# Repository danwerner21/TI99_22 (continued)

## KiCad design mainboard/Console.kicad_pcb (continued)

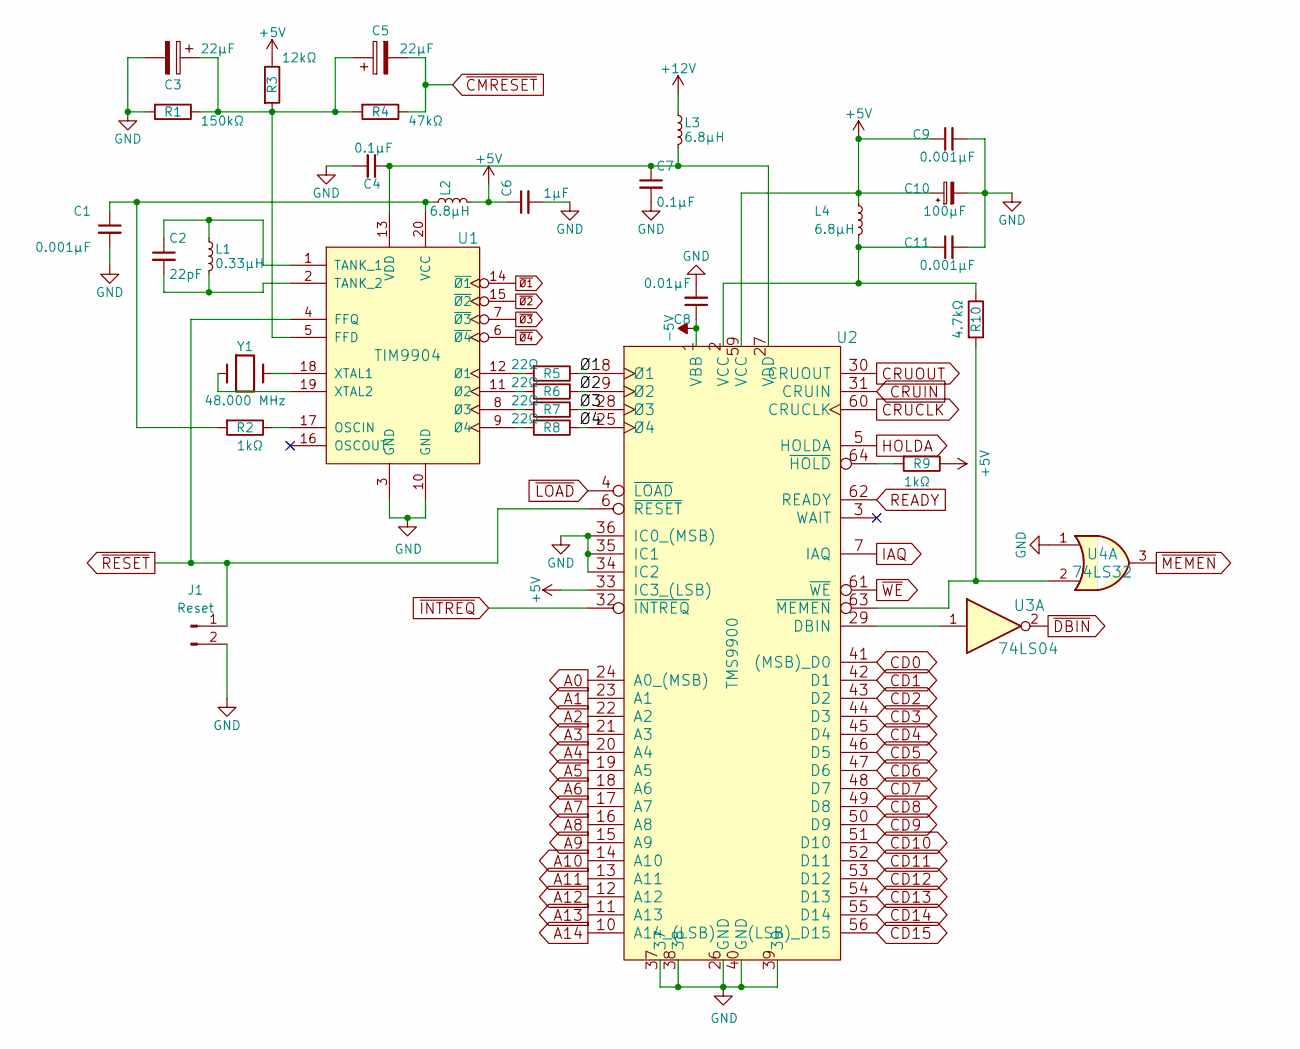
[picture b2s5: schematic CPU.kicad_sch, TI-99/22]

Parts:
C1, C9, C11: 0.001µF; C_Rect_L7.0mm_W2.0mm_P5.00mm
C2: 22pF; C_Rect_L7.0mm_W2.0mm_P5.00mm
C3, C5: 22µF; CP_Radial_D7.5mm_P2.50mm
C4, C7: 0.1µF; C_Rect_L7.0mm_W2.0mm_P5.00mm
C6: 1µF; C_Rect_L7.0mm_W2.0mm_P5.00mm
C8: 0.01µF; C_Rect_L7.0mm_W2.0mm_P5.00mm
C10: 100µF; CP_Radial_D7.5mm_P2.50mm
J1: Reset; PinHeader_1x02_P2.54mm_Vertical
L1: 0.33µH; R_Axial_DIN0207_L6.3mm_D2.5mm_P7.62mm_Horizontal
L2, L3, L4: 6.8µH; R_Axial_DIN0207_L6.3mm_D2.5mm_P7.62mm_Horizontal
R1: 150kΩ; R_Axial_DIN0207_L6.3mm_D2.5mm_P7.62mm_Horizontal
R2, R9: 1kΩ; R_Axial_DIN0207_L6.3mm_D2.5mm_P7.62mm_Horizontal
R3: 12kΩ; R_Axial_DIN0207_L6.3mm_D2.5mm_P7.62mm_Horizontal
R4: 47kΩ; R_Axial_DIN0207_L6.3mm_D2.5mm_P7.62mm_Horizontal
R5, R6, R7, R8: 22Ω; R_Axial_DIN0207_L6.3mm_D2.5mm_P7.62mm_Horizontal
R10: 4.7kΩ; R_Axial_DIN0207_L6.3mm_D2.5mm_P7.62mm_Horizontal
U1: TIM9904; DIP-20_W7.62mm_Socket_LongPads
U2: TMS9900; DIP-64_W22.86mm_Socket_LongPads
U3: 74LS04; DIP-14_W7.62mm_Socket_LongPads
U4: 74LS32; DIP-14_W7.62mm_Socket_LongPads
Y1: 48.000 MHz; Crystal_HC49-U_Vertical

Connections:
+5V: C6.1, C9.1, C10.1, L2.2, L4.1, R3.1, R9.1, U2.33 (IC3_(LSB)), U2.59 (VCC); also elsewhere on the board
+12V: L3.1; also elsewhere on the board
-5V: C8.1, U2.1 (VBB); also elsewhere on the board
/CPU/Ø1: R5.1, U2.8 (Ø1)
/CPU/Ø2: R6.1, U2.9 (Ø2)
/CPU/Ø3: R7.1, U2.28 (Ø3)
/CPU/Ø4: R8.1, U2.25 (Ø4)
A0: U2.24 (A0_(MSB)); also elsewhere on the board
A1: U2.23 (A1); also elsewhere on the board
A2: U2.22 (A2); also elsewhere on the board
A3: U2.21 (A3); also elsewhere on the board
A4: U2.20 (A4); also elsewhere on the board
A5: U2.19 (A5); also elsewhere on the board
A6: U2.18 (A6); also elsewhere on the board
A7: U2.17 (A7); also elsewhere on the board
A8: U2.16 (A8); also elsewhere on the board
A9: U2.15 (A9); also elsewhere on the board
A10: U2.14 (A10); also elsewhere on the board
A11: U2.13 (A11); also elsewhere on the board
A12: U2.12 (A12); also elsewhere on the board
A13: U2.11 (A13); also elsewhere on the board
A14: U2.10 (A14_(LSB)); also elsewhere on the board
CD0: U2.41 ((MSB)_D0); also elsewhere on the board
CD1: U2.42 (D1); also elsewhere on the board
CD2: U2.43 (D2); also elsewhere on the board
CD3: U2.44 (D3); also elsewhere on the board
CD4: U2.45 (D4); also elsewhere on the board
CD5: U2.46 (D5); also elsewhere on the board
CD6: U2.47 (D6); also elsewhere on the board
CD7: U2.48 (D7); also elsewhere on the board
CD8: U2.49 (D8); also elsewhere on the board
CD9: U2.50 (D9); also elsewhere on the board
CD10: U2.51 (D10); also elsewhere on the board
CD11: U2.52 (D11); also elsewhere on the board
CD12: U2.53 (D12); also elsewhere on the board
CD13: U2.54 (D13); also elsewhere on the board
CD14: U2.55 (D14); also elsewhere on the board
CD15: U2.56 ((LSB)_D15); also elsewhere on the board
CRUCLK: U2.60 (CRUCLK); also elsewhere on the board
CRUIN: U2.31 (CRUIN); also elsewhere on the board
CRUOUT: U2.30 (CRUOUT); also elsewhere on the board
HOLDA: U2.5 (HOLDA); also elsewhere on the board
IAQ: U2.7 (IAQ); also elsewhere on the board
unnamed: C1.1, L2.1, R2.2, U1.20 (VCC)
unnamed: C2.1, L1.1, U1.1 (TANK_1)
unnamed: C2.2, L1.2, U1.2 (TANK_2)
unnamed: C3.1, C5.1, R1.1, R3.2, R4.2, U1.5 (FFD)
unnamed: C4.1, C7.1, L3.2, U1.13 (VDD), U2.27 (VDD)
unnamed: C11.1, L4.2, R10.1, U2.2 (VCC)
unnamed: R2.1, U1.17 (OSCIN)
unnamed: R5.2, U1.12 (Ø1)
unnamed: R6.2, U1.11 (Ø2)
unnamed: R7.2, U1.8 (Ø3)
unnamed: R8.2, U1.9 (Ø4)
unnamed: R9.2, U2.64 (~HOLD)
unnamed: R10.2, U2.63 (~MEMEN), U4.2
unnamed: U1.18 (XTAL1), Y1.2
unnamed: U1.19 (XTAL2), Y1.1
unnamed: U2.29 (DBIN), U3.1
READY: U2.62 (READY); also elsewhere on the board
VRAM_BANK: C1.2, C3.2, C4.2, C6.2, C7.2, C8.2, C9.2, C10.2, C11.2, J1.2, R1.2, U1.3 (GND), U1.10 (GND), U2.26 (GND), U2.34 (IC2), U2.35 (IC1), U2.36 (IC0_(MSB)), U2.37, U2.38, U2.39, U2.40 (GND), U4.1; also elsewhere on the board
~CMRESET: C5.2, R4.1; also elsewhere on the board
~DBIN: U3.2; also elsewhere on the board
~INTREQ: U2.32 (~INTREQ); also elsewhere on the board
~LOAD: U2.4 (~LOAD); also elsewhere on the board
~MEMEN: U4.3; also elsewhere on the board
~RESET: J1.1, U1.4 (FFQ), U2.6 (~RESET); also elsewhere on the board
~WE: U2.61 (~WE); also elsewhere on the board
~Ø1: U1.14 (~Ø1); also elsewhere on the board
~Ø2: U1.15 (~Ø2); also elsewhere on the board
~Ø3: U1.7 (~Ø3); also elsewhere on the board
~Ø4: U1.6 (~Ø4); also elsewhere on the board

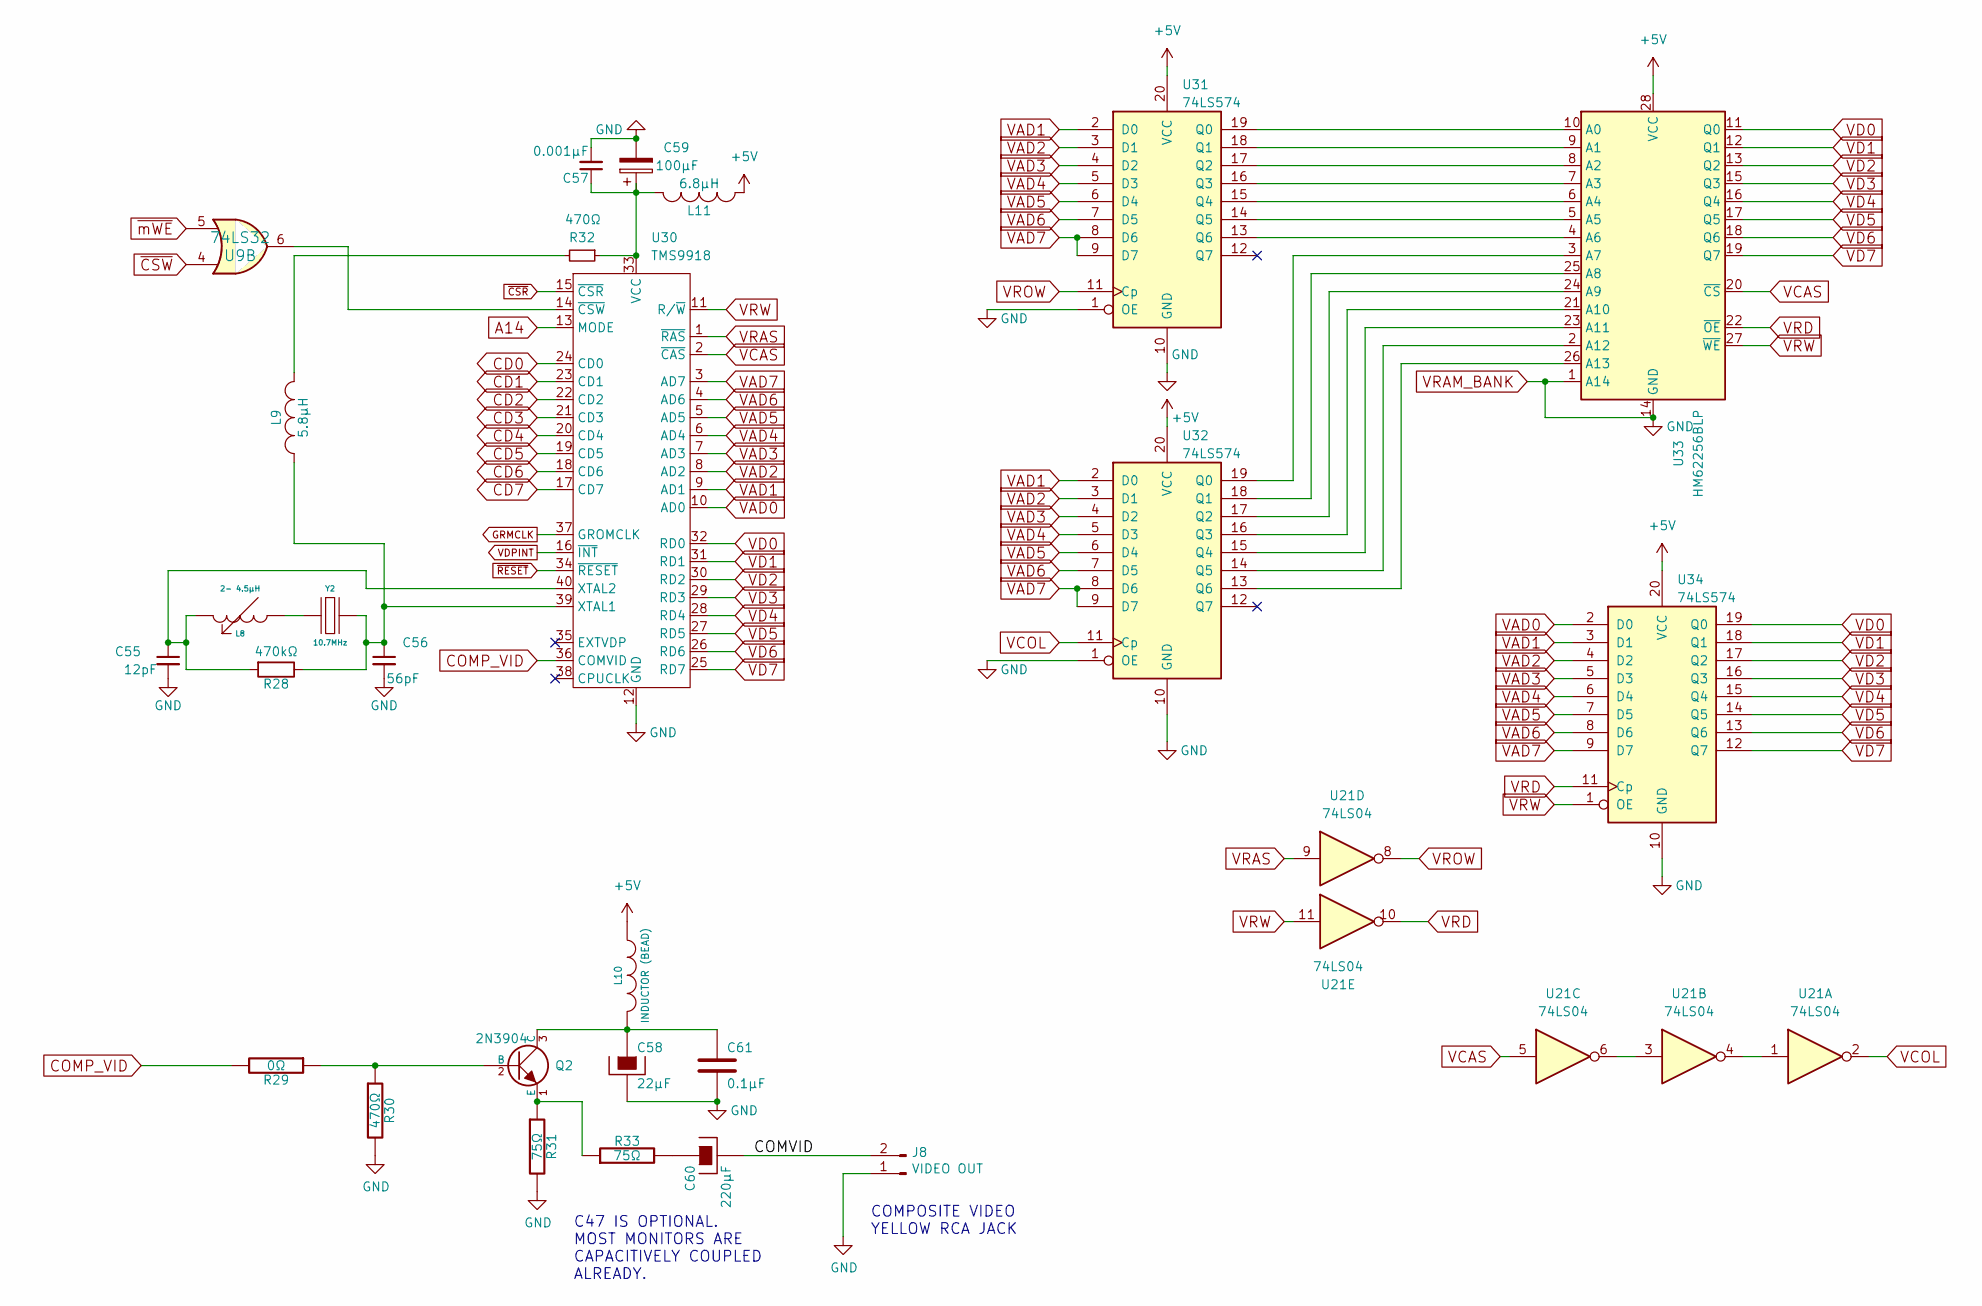
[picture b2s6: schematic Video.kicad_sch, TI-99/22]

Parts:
C55: 12pF; C_Rect_L7.0mm_W2.0mm_P5.00mm
C56: 56pF; C_Rect_L7.0mm_W2.0mm_P5.00mm
C57: 0.001µF; C_Rect_L7.0mm_W2.0mm_P5.00mm
C58: 22µF; CP_Radial_D7.5mm_P2.50mm
C59: 100µF; CP_Radial_D7.5mm_P2.50mm
C60: 220µF; CP_Radial_D7.5mm_P2.50mm
C61: 0.1µF; C_Rect_L7.0mm_W2.0mm_P5.00mm
J8: VIDEO OUT; PinHeader_1x02_P2.54mm_Vertical
L8: 2- 4.5µH; R_Axial_DIN0207_L6.3mm_D2.5mm_P7.62mm_Horizontal
L9: 5.8µH; R_Axial_DIN0207_L6.3mm_D2.5mm_P7.62mm_Horizontal
L10: INDUCTOR (BEAD); R_Axial_DIN0207_L6.3mm_D2.5mm_P10.16mm_Horizontal
L11: 6.8µH; R_Axial_DIN0207_L6.3mm_D2.5mm_P7.62mm_Horizontal
Q2: 2N3904; TO-92L_HandSolder
R28: 470kΩ; R_Axial_DIN0207_L6.3mm_D2.5mm_P7.62mm_Horizontal
R29: 0Ω; R_Axial_DIN0207_L6.3mm_D2.5mm_P7.62mm_Horizontal
R30, R32: 470Ω; R_Axial_DIN0207_L6.3mm_D2.5mm_P7.62mm_Horizontal
R31, R33: 75Ω; R_Axial_DIN0207_L6.3mm_D2.5mm_P7.62mm_Horizontal
U9: 74LS32; DIP-14_W7.62mm_Socket_LongPads
U21: 74LS04; DIP-14_W7.62mm_Socket_LongPads
U30: TMS9918; DIP-40_W15.24mm_Socket_LongPads
U31, U32, U34: 74LS574; DIP-20_W7.62mm_Socket_LongPads
U33: HM62256BLP; DIP-28_W15.24mm_Socket_LongPads
Y2: 10.7MHz; Crystal_HC49-U_Vertical

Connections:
+5V: L10.1, L11.2, U31.20 (VCC), U32.20 (VCC), U33.28 (VCC), U34.20 (VCC); also elsewhere on the board
/Video/COMVID: C60.2, J8.2
A14: U30.13 (MODE); also elsewhere on the board
CD0: U30.24 (CD0); also elsewhere on the board
CD1: U30.23 (CD1); also elsewhere on the board
CD2: U30.22 (CD2); also elsewhere on the board
CD3: U30.21 (CD3); also elsewhere on the board
CD4: U30.20 (CD4); also elsewhere on the board
CD5: U30.19 (CD5); also elsewhere on the board
CD6: U30.18 (CD6); also elsewhere on the board
CD7: U30.17 (CD7); also elsewhere on the board
COMP_VID: R29.2, U30.36 (COMVID)
GRMCLK: U30.37 (GROMCLK); also elsewhere on the board
unnamed: C55.1, L8.2, R28.2, U30.40 (XTAL2)
unnamed: C56.1, L9.1, R28.1, U30.39 (XTAL1), Y2.2
unnamed: C57.1, C59.1, L11.1, R32.1, U30.33 (VCC)
unnamed: C58.1, C61.1, L10.2, Q2.3 (C)
unnamed: C60.1, R33.2
unnamed: L8.1, Y2.1
unnamed: L9.2, R32.2
unnamed: Q2.1 (E), R31.1, R33.1
unnamed: Q2.2 (B), R29.1, R30.1
unnamed: U21.1, U21.4
unnamed: U21.3, U21.6
unnamed: U9.6, U30.14 (~CSW)
unnamed: U31.13 (Q6), U33.4 (A6)
unnamed: U31.14 (Q5), U33.5 (A5)
unnamed: U31.15 (Q4), U33.6 (A4)
unnamed: U31.16 (Q3), U33.7 (A3)
unnamed: U31.17 (Q2), U33.8 (A2)
unnamed: U31.18 (Q1), U33.9 (A1)
unnamed: U31.19 (Q0), U33.10 (A0)
unnamed: U32.13 (Q6), U33.26 (A13)
unnamed: U32.14 (Q5), U33.2 (A12)
unnamed: U32.15 (Q4), U33.23 (A11)
unnamed: U32.16 (Q3), U33.21 (A10)
unnamed: U32.17 (Q2), U33.24 (A9)
unnamed: U32.18 (Q1), U33.25 (A8)
unnamed: U32.19 (Q0), U33.3 (A7)
VAD0: U30.10 (AD0), U34.2 (D0)
VAD1: U30.9 (AD1), U31.2 (D0), U32.2 (D0), U34.3 (D1)
VAD2: U30.8 (AD2), U31.3 (D1), U32.3 (D1), U34.4 (D2)
VAD3: U30.7 (AD3), U31.4 (D2), U32.4 (D2), U34.5 (D3)
VAD4: U30.6 (AD4), U31.5 (D3), U32.5 (D3), U34.6 (D4)
VAD5: U30.5 (AD5), U31.6 (D4), U32.6 (D4), U34.7 (D5)
VAD6: U30.4 (AD6), U31.7 (D5), U32.7 (D5), U34.8 (D6)
VAD7: U30.3 (AD7), U31.8 (D6), U31.9 (D7), U32.8 (D6), U32.9 (D7), U34.9 (D7)
VCAS: U21.5, U30.2 (~CAS), U33.20 (~CS)
VCOL: U21.2, U32.11 (Cp)
VD0: U30.32 (RD0), U33.11 (Q0), U34.19 (Q0)
VD1: U30.31 (RD1), U33.12 (Q1), U34.18 (Q1)
VD2: U30.30 (RD2), U33.13 (Q2), U34.17 (Q2)
VD3: U30.29 (RD3), U33.15 (Q3), U34.16 (Q3)
VD4: U30.28 (RD4), U33.16 (Q4), U34.15 (Q4)
VD5: U30.27 (RD5), U33.17 (Q5), U34.14 (Q5)
VD6: U30.26 (RD6), U33.18 (Q6), U34.13 (Q6)
VD7: U30.25 (RD7), U33.19 (Q7), U34.12 (Q7)
VDPINT: U30.16 (~INT); also elsewhere on the board
VRAM_BANK: C55.2, C56.2, C57.2, C58.2, C59.2, C61.2, J8.1, R30.2, R31.2, U30.12 (GND), U31.1 (OE), U31.10 (GND), U32.1 (OE), U32.10 (GND), U33.1 (A14), U33.14 (GND), U34.10 (GND); also elsewhere on the board
VRAS: U21.9, U30.1 (~RAS)
VRD: U21.10, U33.22 (~OE), U34.11 (Cp)
VROW: U21.8, U31.11 (Cp)
VRW: U21.11, U30.11 (R/~W), U33.27 (~WE), U34.1 (OE)
~CSR: U30.15 (~CSR); also elsewhere on the board
~CSW: U9.4; also elsewhere on the board
~RESET: U30.34 (~RESET); also elsewhere on the board
~mWE: U9.5; also elsewhere on the board

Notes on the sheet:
COMPOSITE VIDEO YELLOW RCA JACK
C47 IS OPTIONAL. MOST MONITORS ARE CAPACITIVELY COUPLED ALREADY.

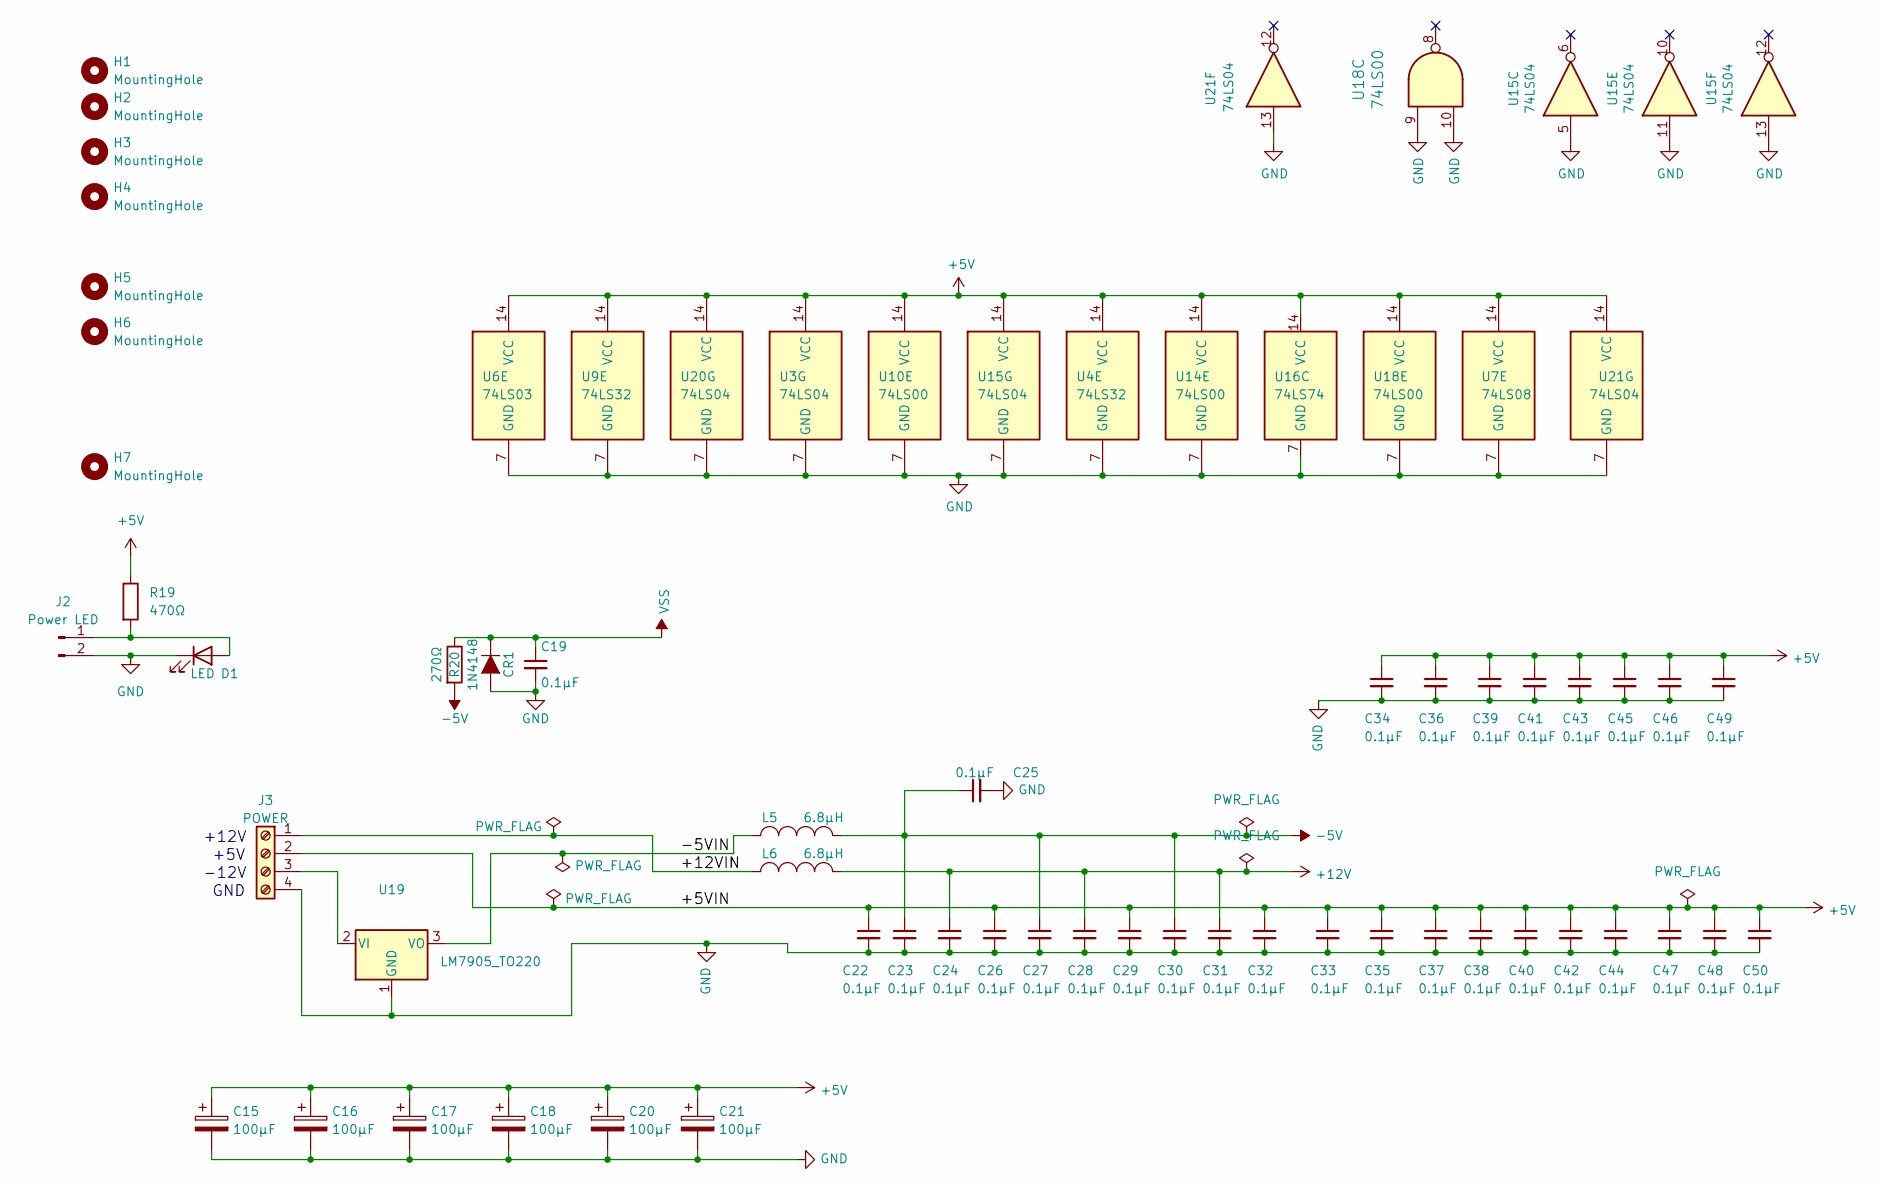
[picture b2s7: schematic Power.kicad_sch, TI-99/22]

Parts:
C15, C16, C17, C18, C20, C21: 100µF; CP_Radial_D7.5mm_P2.50mm
C19, C22, C23, C24, C25, C26, C27, C28, C29, C30, C31, C32, C33, C34, C35, C36, C37, C38, C39, C40, C41, C42, C43, C44, C45, C46, C47, C48, C49, C50: 0.1µF; C_Rect_L7.0mm_W2.0mm_P5.00mm
CR1: 1N4148; D_A-405_P7.62mm_Horizontal
D1: LED; LED_D5.0mm
H1, H2, H3, H4, H5, H6, H7: MountingHole; MountingHole_3.2mm_M3
J2: Power LED; PinHeader_1x02_P2.54mm_Vertical
J3: POWER; TerminalBlock_RND_205-00278_1x04_P5.00mm_Vertical
L5, L6: 6.8µH; R_Axial_DIN0207_L6.3mm_D2.5mm_P7.62mm_Horizontal
R19: 470Ω; R_Axial_DIN0207_L6.3mm_D2.5mm_P7.62mm_Horizontal
R20: 270Ω; R_Axial_DIN0207_L6.3mm_D2.5mm_P7.62mm_Horizontal
U3, U15, U20, U21: 74LS04; DIP-14_W7.62mm_Socket_LongPads
U4, U9: 74LS32; DIP-14_W7.62mm_Socket_LongPads
U6: 74LS03; DIP-14_W7.62mm_Socket_LongPads
U7: 74LS08; DIP-14_W7.62mm_Socket_LongPads
U10, U14, U18: 74LS00; DIP-14_W7.62mm_Socket_LongPads
U16: 74LS74; DIP-14_W7.62mm_Socket_LongPads
U19: LM7905_TO220; TO-220-3_Vertical

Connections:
+5V: C15.1, C16.1, C17.1, C18.1, C20.1, C21.1, C22.1, C26.1, C29.1, C32.1, C33.1, C34.1, C35.1, C36.1, C37.1, C38.1, C39.1, C40.1, C41.1, C42.1, C43.1, C44.1, C45.1, C46.1, C47.1, C48.1, C49.1, C50.1, J3.2, R19.1, U3.14 (VCC), U4.14 (VCC), U6.14 (VCC), U7.14 (VCC), U9.14 (VCC), U10.14 (VCC), U14.14 (VCC), U15.14 (VCC), U16.14 (VCC), U18.14 (VCC), U20.14 (VCC), U21.14 (VCC); also elsewhere on the board
+12V: C24.1, C28.1, C31.1, L6.1; also elsewhere on the board
-5V: C23.1, C25.1, C27.1, C30.1, L5.1, R20.2; also elsewhere on the board
/Power/+12VIN: J3.1, L6.2
/Power/-5VIN: L5.2, U19.3 (VO)
unnamed: D1.2 (A), J2.1, R19.2
unnamed: J3.3, U19.2 (VI)
VRAM_BANK: C15.2, C16.2, C17.2, C18.2, C19.2, C20.2, C21.2, C22.2, C23.2, C24.2, C25.2, C26.2, C27.2, C28.2, C29.2, C30.2, C31.2, C32.2, C33.2, C34.2, C35.2, C36.2, C37.2, C38.2, C39.2, C40.2, C41.2, C42.2, C43.2, C44.2, C45.2, C46.2, C47.2, C48.2, C49.2, C50.2, CR1.2 (A), D1.1 (K), J2.2, J3.4, U3.7 (GND), U4.7 (GND), U6.7 (GND), U7.7 (GND), U9.7 (GND), U10.7 (GND), U14.7 (GND), U15.5, U15.7 (GND), U15.11, U15.13, U16.7 (GND), U18.7 (GND), U18.9, U18.10, U19.1 (GND), U20.7 (GND), U21.7 (GND), U21.13; also elsewhere on the board
VSS: C19.1, CR1.1 (K), R20.1; also elsewhere on the board

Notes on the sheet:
-12V
+5V
GND
+12V

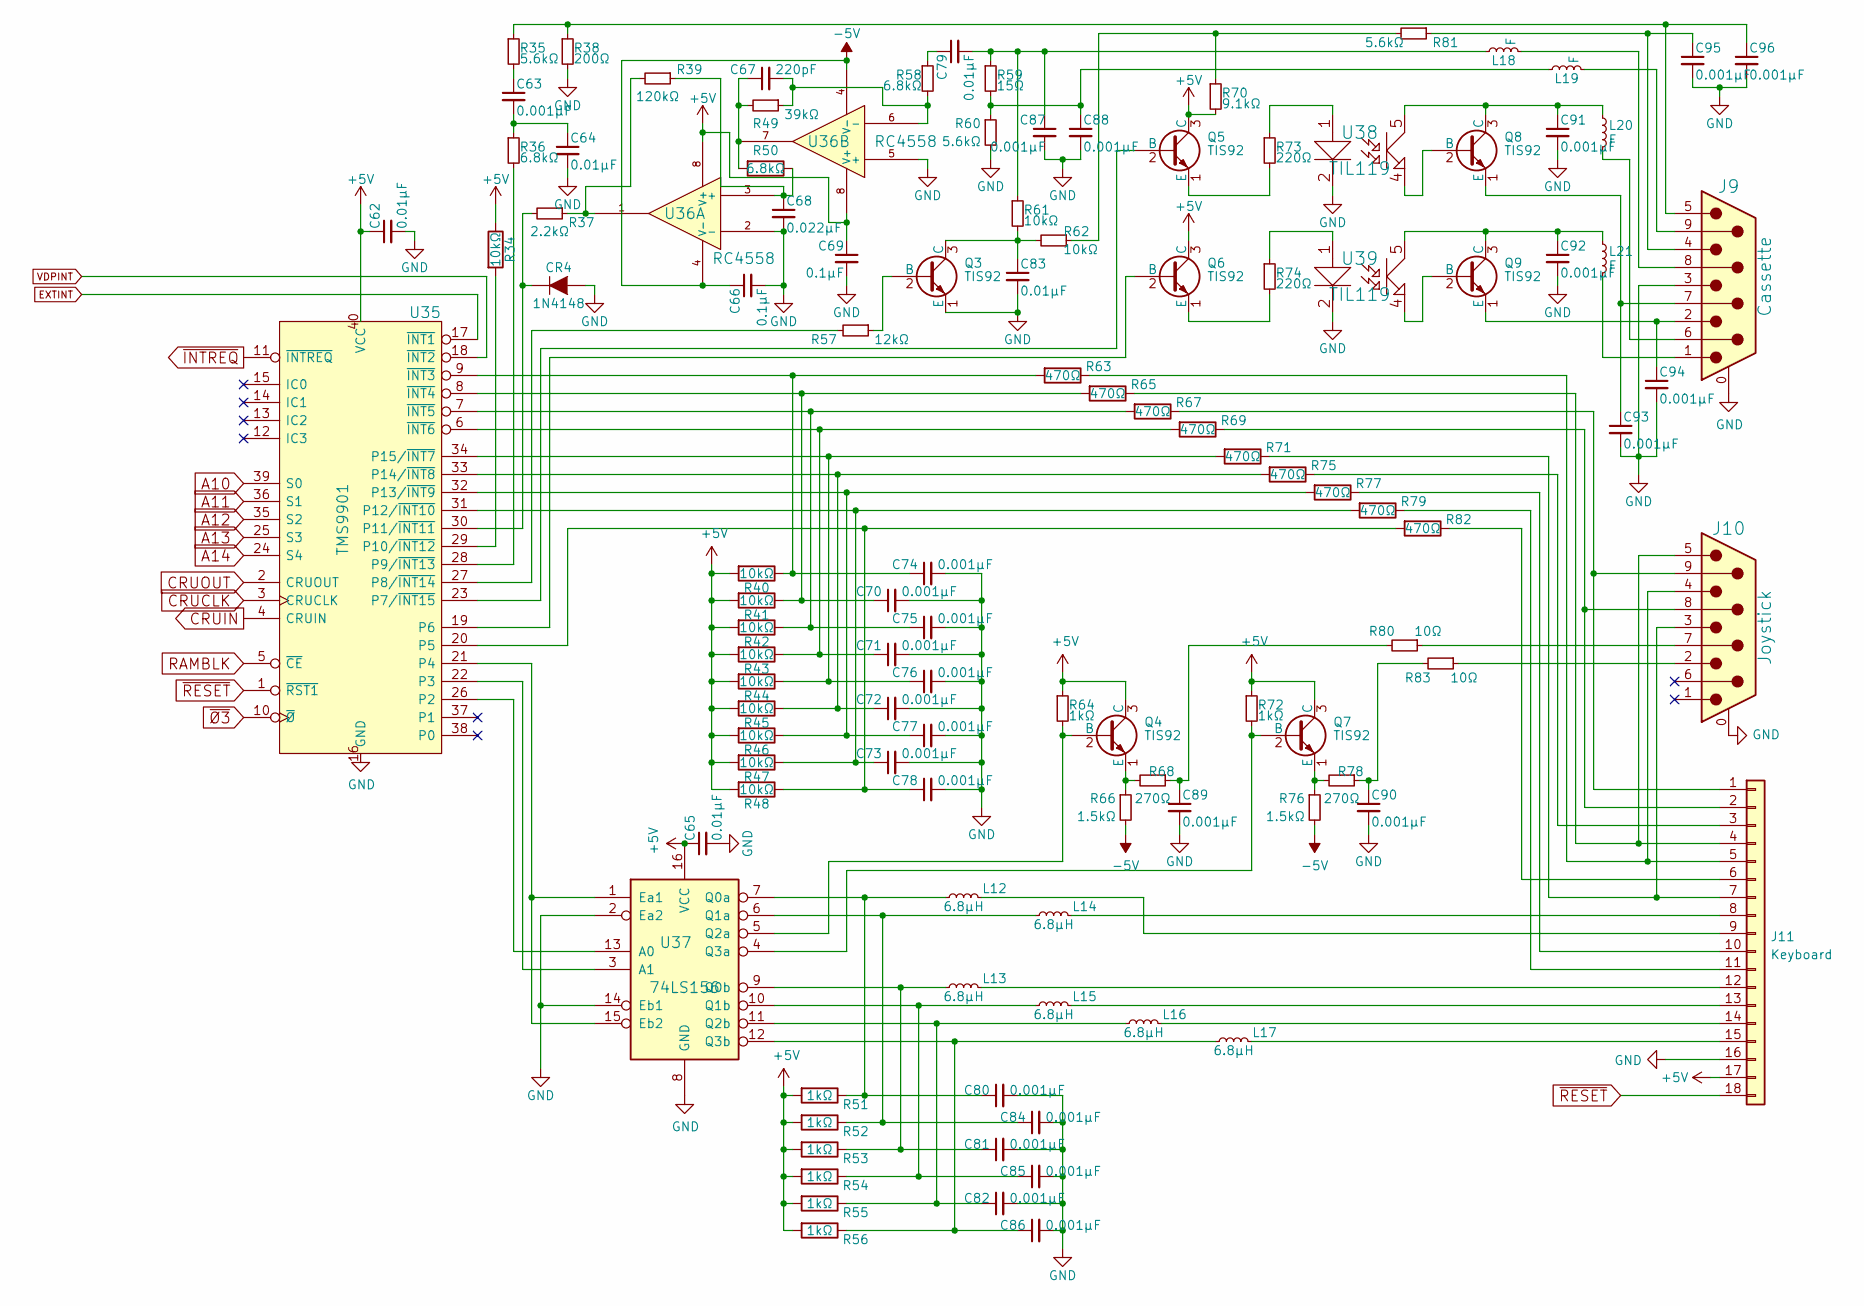
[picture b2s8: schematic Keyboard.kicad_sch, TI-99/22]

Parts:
C62, C64, C65, C79, C83: 0.01µF; C_Rect_L7.0mm_W2.0mm_P5.00mm
C63, C70, C71, C72, C73, C74, C75, C76, C77, C78, C80, C81, C82, C84, C85, C86, C87, C88, C89, C90, C91, C92, C93, C94, C95, C96: 0.001µF; C_Rect_L7.0mm_W2.0mm_P5.00mm
C66, C69: 0.1µF; C_Rect_L7.0mm_W2.0mm_P5.00mm
C67: 220pF; C_Rect_L7.0mm_W2.0mm_P5.00mm
C68: 0.022µF; C_Rect_L7.0mm_W2.0mm_P5.00mm
CR4: 1N4148; D_A-405_P7.62mm_Horizontal
J9: Cassette; DSUB-9_Female_Horizontal_P2.77x2.84mm_EdgePinOffset4.94mm_H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
J10: Joystick; DSUB-9_Female_Horizontal_P2.77x2.84mm_EdgePinOffset4.94mm_H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
J11: Keyboard; PinHeader_1x18_P2.54mm_Vertical
L12, L13, L14, L15, L16, L17: 6.8µH; R_Axial_DIN0207_L6.3mm_D2.5mm_P7.62mm_Horizontal
L18, L19, L20, L21: F; R_Axial_DIN0207_L6.3mm_D2.5mm_P7.62mm_Horizontal
Q3, Q4, Q5, Q6, Q7, Q8, Q9: TIS92; TO-92_HandSolder
R34, R40, R41, R42, R43, R44, R45, R46, R47, R48, R61, R62: 10kΩ; R_Axial_DIN0207_L6.3mm_D2.5mm_P7.62mm_Horizontal
R35, R60, R81: 5.6kΩ; R_Axial_DIN0207_L6.3mm_D2.5mm_P7.62mm_Horizontal
R36, R50, R58: 6.8kΩ; R_Axial_DIN0207_L6.3mm_D2.5mm_P7.62mm_Horizontal
R37: 2.2kΩ; R_Axial_DIN0207_L6.3mm_D2.5mm_P7.62mm_Horizontal
R38: 200Ω; R_Axial_DIN0207_L6.3mm_D2.5mm_P7.62mm_Horizontal
R39: 120kΩ; R_Axial_DIN0207_L6.3mm_D2.5mm_P7.62mm_Horizontal
R49: 39kΩ; R_Axial_DIN0207_L6.3mm_D2.5mm_P7.62mm_Horizontal
R51, R52, R53, R54, R55, R56, R64, R72: 1kΩ; R_Axial_DIN0207_L6.3mm_D2.5mm_P7.62mm_Horizontal
R57: 12kΩ; R_Axial_DIN0207_L6.3mm_D2.5mm_P7.62mm_Horizontal
R59: 15Ω; R_Axial_DIN0207_L6.3mm_D2.5mm_P7.62mm_Horizontal
R63, R65, R67, R69, R71, R75, R77, R79, R82: 470Ω; R_Axial_DIN0207_L6.3mm_D2.5mm_P7.62mm_Horizontal
R66, R76: 1.5kΩ; R_Axial_DIN0207_L6.3mm_D2.5mm_P7.62mm_Horizontal
R68, R78: 270Ω; R_Axial_DIN0207_L6.3mm_D2.5mm_P7.62mm_Horizontal
R70: 9.1kΩ; R_Axial_DIN0207_L6.3mm_D2.5mm_P7.62mm_Horizontal
R73, R74: 220Ω; R_Axial_DIN0207_L6.3mm_D2.5mm_P7.62mm_Horizontal
R80, R83: 10Ω; R_Axial_DIN0207_L6.3mm_D2.5mm_P7.62mm_Horizontal
U35: TMS9901; DIP-40_W15.24mm_Socket_LongPads
U36: RC4558; DIP-8_W7.62mm_Socket_LongPads
U37: 74LS156; DIP-16_W7.62mm_Socket_LongPads
U38, U39: TIL119; DIP-6_W7.62mm_Socket_LongPads

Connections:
+5V: C62.1, C65.1, C69.1, J11.17, Q4.3 (C), Q5.3 (C), Q6.3 (C), Q7.3 (C), R34.1, R40.2, R41.2, R42.2, R43.2, R44.2, R45.2, R46.2, R47.2, R48.2, R51.2, R52.2, R53.2, R54.2, R55.2, R56.2, R64.1, R70.2, R72.1, U35.40 (VCC), U36.8 (V+), U37.16 (VCC); also elsewhere on the board
-5V: C66.1, R66.2, R76.2, U36.4 (V-); also elsewhere on the board
A10: U35.39 (S0); also elsewhere on the board
A11: U35.36 (S1); also elsewhere on the board
A12: U35.35 (S2); also elsewhere on the board
A13: U35.25 (S3); also elsewhere on the board
A14: U35.24 (S4); also elsewhere on the board
CRUCLK: U35.3 (CRUCLK); also elsewhere on the board
CRUIN: U35.4 (CRUIN); also elsewhere on the board
CRUOUT: U35.2 (CRUOUT); also elsewhere on the board
EXTINT: U35.17 (~INT1); also elsewhere on the board
unnamed: C63.1, R35.2
unnamed: C63.2, C64.1, R36.1
unnamed: C67.1, R49.2, R50.2, U36.7
unnamed: C67.2, R49.1, R58.2, U36.6 (-)
unnamed: C68.1, R39.1, R50.1, U36.3 (+)
unnamed: C70.1, R41.1, R65.2, U35.8 (~INT4)
unnamed: C71.1, R43.1, R69.2, U35.6 (~INT6)
unnamed: C72.1, R45.1, R75.2, U35.33 (P14/~INT8)
unnamed: C73.1, R47.1, R79.2, U35.31 (P12/~INT10)
unnamed: C74.1, R40.1, R63.2, U35.9 (~INT3)
unnamed: C75.1, R42.1, R67.2, U35.7 (~INT5)
unnamed: C76.1, R44.1, R71.2, U35.34 (P15/~INT7)
unnamed: C77.1, R46.1, R77.2, U35.32 (P13/~INT9)
unnamed: C78.1, R48.1, R82.2, U35.20 (P5)
unnamed: C79.1, R58.1
unnamed: C79.2, C87.1, L18.1, R59.1, R61.1
unnamed: C80.1, L12.1, R51.1, U37.7 (Q0a)
unnamed: C81.1, L13.1, R53.1, U37.9 (Q0b)
unnamed: C82.1, L16.1, R55.1, U37.11 (Q2b)
unnamed: C83.1, Q3.3 (C), R61.2, R62.2
unnamed: C84.1, L14.1, R52.1, U37.6 (Q1a)
unnamed: C85.1, L15.1, R54.1, U37.10 (Q1b)
unnamed: C86.1, L17.1, R56.1, U37.12 (Q3b)
unnamed: C88.1, L19.1, R59.2, R60.1
unnamed: C89.1, R68.1, R80.2
unnamed: C90.1, R78.1, R83.2
unnamed: C91.1, L20.1, Q8.3 (C), U38.5
unnamed: C92.1, L21.1, Q9.3 (C), U39.5
unnamed: C93.1, J9.7, Q8.1 (E)
unnamed: C94.1, J9.2, Q9.1 (E)
unnamed: C95.1, J9.4, R81.1
unnamed: C96.1, J9.5, R35.1, R38.1
unnamed: CR4.1 (K), R37.2, U35.30 (P11/~INT11)
unnamed: J9.1, L21.2
unnamed: J9.6, L20.2
unnamed: J9.8, L18.2
unnamed: J9.9, L19.2
unnamed: J10.2, R83.1
unnamed: J10.3, J11.7, R71.1
unnamed: J10.4, J11.5, R63.1
unnamed: J10.5, J11.4, R65.1
unnamed: J10.7, R80.1
unnamed: J10.8, J11.2, R69.1
unnamed: J10.9, J11.1, R67.1
unnamed: J11.3, R75.1
unnamed: J11.6, R82.1
unnamed: J11.8, L14.2
unnamed: J11.9, L12.2
unnamed: J11.10, R77.1
unnamed: J11.11, R79.1
unnamed: J11.12, L13.2
unnamed: J11.13, L15.2
unnamed: J11.14, L16.2
unnamed: J11.15, L17.2
unnamed: Q3.2 (B), R57.1
unnamed: Q4.1 (E), R66.1, R68.2
unnamed: Q4.2 (B), R64.2, U37.5 (Q2a)
unnamed: Q5.1 (E), R73.2
unnamed: Q5.2 (B), U35.23 (P7/~INT15)
unnamed: Q6.1 (E), R74.2
unnamed: Q6.2 (B), U35.19 (P6)
unnamed: Q7.1 (E), R76.1, R78.2
unnamed: Q7.2 (B), R72.2, U37.4 (Q3a)
unnamed: Q8.2 (B), U38.4 (KK)
unnamed: Q9.2 (B), U39.4 (KK)
unnamed: R34.2, U35.29 (P10/~INT12)
unnamed: R36.2, U35.28 (P9/~INT13)
unnamed: R37.1, R39.2, U36.1
unnamed: R57.2, U35.27 (P8/~INT14)
unnamed: R62.1, R70.1, R81.2
unnamed: R73.1, U38.1 (A)
unnamed: R74.1, U39.1 (A)
unnamed: U35.21 (P4), U37.1 (Ea1), U37.15 (Eb2)
unnamed: U35.22 (P3), U37.3 (A1)
unnamed: U35.26 (P2), U37.13 (A0)
RAMBLK: U35.5 (~CE); also elsewhere on the board
VDPINT: U35.18 (~INT2); also elsewhere on the board
VRAM_BANK: C62.2, C64.2, C65.2, C66.2, C68.2, C69.2, C70.2, C71.2, C72.2, C73.2, C74.2, C75.2, C76.2, C77.2, C78.2, C80.2, C81.2, C82.2, C83.2, C84.2, C85.2, C86.2, C87.2, C88.2, C89.2, C90.2, C91.2, C92.2, C93.2, C94.2, C95.2, C96.2, CR4.2 (A), J9.0 (PAD), J9.3, J10.0 (PAD), J11.16, Q3.1 (E), R38.2, R60.2, U35.16 (GND), U36.2 (-), U36.5 (+), U37.2 (Ea2), U37.8 (GND), U37.14 (Eb1), U38.2 (K), U39.2 (K); also elsewhere on the board
~INTREQ: U35.11 (~INTREQ); also elsewhere on the board
~RESET: J11.18, U35.1 (~RST1); also elsewhere on the board
~Ø3: U35.10 (~Ø); also elsewhere on the board

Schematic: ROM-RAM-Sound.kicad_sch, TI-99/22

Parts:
C52: 100µF; CP_Radial_D5.0mm_P2.00mm
C53, C54: 0.1µF; C_Rect_L7.0mm_W2.0mm_P5.00mm
J5, J6: ROM Select; PinHeader_1x03_P2.54mm_Vertical
J7: AUDIO OUT; PinHeader_1x02_P2.54mm_Vertical
L7: 6.8µH; R_Axial_DIN0207_L6.3mm_D2.5mm_P7.62mm_Horizontal
R27: 10Ω; R_Axial_DIN0207_L6.3mm_D2.5mm_P7.62mm_Horizontal
U25, U26: HM62256BLP; DIP-28_W15.24mm_Socket_LongPads
U27, U28: 27C64; DIP-28_W15.24mm_Socket_LongPads
U29: SN76489; DIP-16_W7.62mm_Socket_LongPads

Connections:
+5V: J5.1, J6.1, L7.1, U25.28 (VCC), U26.28 (VCC), U27.27 (~PGM), U27.28 (VCC), U28.27 (~PGM), U28.28 (VCC); also elsewhere on the board
A0: U25.10 (A0), U26.10 (A0); also elsewhere on the board
A1: U25.9 (A1), U26.9 (A1); also elsewhere on the board
A2: U25.8 (A2), U26.8 (A2); also elsewhere on the board
A3: U25.7 (A3), U26.7 (A3), U27.23 (A11), U28.23 (A11); also elsewhere on the board
A4: U25.6 (A4), U26.6 (A4), U27.21 (A10), U28.21 (A10); also elsewhere on the board
A5: U25.5 (A5), U26.5 (A5), U27.24 (A9), U28.24 (A9); also elsewhere on the board
A6: U25.4 (A6), U26.4 (A6), U27.25 (A8), U28.25 (A8); also elsewhere on the board
A7: U25.3 (A7), U26.3 (A7), U27.3 (A7), U28.3 (A7); also elsewhere on the board
A8: U25.25 (A8), U26.25 (A8), U27.4 (A6), U28.4 (A6); also elsewhere on the board
A9: U25.24 (A9), U26.24 (A9), U27.5 (A5), U28.5 (A5); also elsewhere on the board
A10: U25.21 (A10), U26.21 (A10), U27.6 (A4), U28.6 (A4); also elsewhere on the board
A11: U25.23 (A11), U26.23 (A11), U27.7 (A3), U28.7 (A3); also elsewhere on the board
A12: U25.2 (A12), U26.2 (A12), U27.8 (A2), U28.8 (A2); also elsewhere on the board
A13: U25.26 (A13), U26.26 (A13), U27.9 (A1), U28.9 (A1); also elsewhere on the board
A14: U25.1 (A14), U26.1 (A14), U27.10 (A0), U28.10 (A0); also elsewhere on the board
CD0: U25.11 (Q0), U27.19 (D7); also elsewhere on the board
CD1: U25.12 (Q1), U27.18 (D6); also elsewhere on the board
CD2: U25.18 (Q6), U27.17 (D5); also elsewhere on the board
CD3: U25.16 (Q4), U27.16 (D4); also elsewhere on the board
CD4: U25.17 (Q5), U27.15 (D3); also elsewhere on the board
CD5: U25.15 (Q3), U27.13 (D2); also elsewhere on the board
CD6: U25.13 (Q2), U27.12 (D1); also elsewhere on the board
CD7: U25.19 (Q7), U27.11 (D0); also elsewhere on the board
CD8: U26.15 (Q3), U28.19 (D7); also elsewhere on the board
CD9: U26.13 (Q2), U28.18 (D6); also elsewhere on the board
CD10: U26.12 (Q1), U28.17 (D5); also elsewhere on the board
CD11: U26.11 (Q0), U28.16 (D4); also elsewhere on the board
CD12: U26.19 (Q7), U28.15 (D3); also elsewhere on the board
CD13: U26.18 (Q6), U28.13 (D2); also elsewhere on the board
CD14: U26.17 (Q5), U28.12 (D1); also elsewhere on the board
CD15: U26.16 (Q4), U28.11 (D0); also elsewhere on the board
D0: U29.3 (D0); also elsewhere on the board
D1: U29.2 (D1); also elsewhere on the board
D2: U29.1 (D2); also elsewhere on the board
D3: U29.15 (D3); also elsewhere on the board
D4: U29.13 (D4); also elsewhere on the board
D5: U29.12 (D5); also elsewhere on the board
D6: U29.11 (D6); also elsewhere on the board
D7: U29.10 (D7); also elsewhere on the board
GRMCLK: U29.14 (CLK); also elsewhere on the board
unnamed: C52.1, C53.1, U29.7 (AOUT)
unnamed: C53.2, R27.1
unnamed: C54.2, L7.2, U29.16 (VCC)
unnamed: J5.2, U27.2 (A12)
unnamed: J6.2, U28.2 (A12)
READY_~HOLD: U29.4 (READY); also elsewhere on the board
SNDIN: U29.9 (AIN); also elsewhere on the board
SNDOUT: C52.2, J7.1
VRAM_BANK: C54.1, J5.3, J6.3, J7.2, R27.2, U25.14 (GND), U25.22 (~OE), U26.14 (GND), U26.22 (~OE), U27.14 (GND), U27.22 (~OE), U28.14 (GND), U28.22 (~OE), U29.8 (GND); also elsewhere on the board
~RAM: U25.20 (~CS), U26.20 (~CS); also elsewhere on the board
~ROM: U27.20 (~CE), U28.20 (~CE); also elsewhere on the board
~SOUND_SEL: U29.6 (~CE); also elsewhere on the board
~WE: U25.27 (~WE), U26.27 (~WE); also elsewhere on the board
~mWE: U29.5 (~WE); also elsewhere on the board

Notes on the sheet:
AUDIO RED RCA JACK

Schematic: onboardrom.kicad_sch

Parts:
J16: Rom Select 1; PinSocket_1x03_P2.54mm_Vertical
J17: Rom Select 2; PinSocket_1x03_P2.54mm_Vertical
R100: 10kΩ; R_Axial_DIN0207_L6.3mm_D2.5mm_P7.62mm_Horizontal
SW2: Internal Cart ROM Enable; PinHeader_1x02_P2.54mm_Vertical
U43: 74LS379; DIP-16_W7.62mm_Socket_LongPads
U44: 27C010-C; DIP-32_W15.24mm_Socket_LongPads

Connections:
+5V: R100.1, U43.16 (VCC), U44.30 (NC), U44.31 (~PGM), U44.32 (VCC); also elsewhere on the board
A3: U44.4 (A12); also elsewhere on the board
A4: U44.25 (A11); also elsewhere on the board
A5: U44.23 (A10); also elsewhere on the board
A6: U44.26 (A9); also elsewhere on the board
A7: U44.27 (A8); also elsewhere on the board
A8: U44.5 (A7); also elsewhere on the board
A9: U44.6 (A6); also elsewhere on the board
A10: U44.7 (A5); also elsewhere on the board
A11: U43.13 (D3), U44.8 (A4); also elsewhere on the board
A12: U43.12 (D2), U44.9 (A3); also elsewhere on the board
A13: U43.5 (D1), U44.10 (A2); also elsewhere on the board
A15-CRUOUT: U44.12 (A0); also elsewhere on the board
D0: U44.21 (D7); also elsewhere on the board
D1: U44.20 (D6); also elsewhere on the board
D2: U44.19 (D5); also elsewhere on the board
D3: U44.18 (D4); also elsewhere on the board
D4: U44.17 (D3); also elsewhere on the board
D5: U44.15 (D2); also elsewhere on the board
D6: U44.14 (D1); also elsewhere on the board
D7: U44.13 (D0); also elsewhere on the board
IO_A14: U43.4 (D0), U44.11 (A1); also elsewhere on the board
IR_A1: J17.3, U43.10 (Q2)
IR_A1_O: J17.2, U44.3 (A15)
IR_A2: J16.3, U43.7 (Q1)
IR_A2_O: J16.2, U44.29 (A14)
unnamed: U43.2 (Q0), U44.28 (A13)
unnamed: U43.15 (Q3), U44.2 (A16)
VRAM_BANK: J16.1, J17.1, U43.8 (GND), U44.1 (VPP), U44.16 (GND), U44.22 (~CE); also elsewhere on the board
~IROMG: R100.2, SW2.2, U43.1 (~E), U44.24 (~OE)
~ROMG: SW2.1; also elsewhere on the board
~mWE: U43.9 (CP); also elsewhere on the board

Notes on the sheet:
27C010 J17-2&3 J18-2&3 27C512 J17-2&3 J18-2&3 27C256 J17-1&2 J18-2&3 27C128 J17-1&2 J18-1&2 27C64 J17-1&2 J18-1&2

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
